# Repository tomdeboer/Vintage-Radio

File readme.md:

*Vintage Radio*
----
This project started out a birthday gift for a friend, but has changed shape many times over the years. The idea was to take a '60s vintage radio and upgrade it as well as I can with stereo, bluetooth, IR remote control, motorised volume knobs and quality >50 W speakers.

Now that the project is really taking shape, I thought: why not make the code and documents open source!

**Note: this is a work in progress at the moment.**

### What can it do?
As mentioned, the radio packs some serious punch when it comes to audio. It can play your tunes loudly and clearly. It also has a bluetooth receiver so you can stream your audio wirelessly. In addition to bluetooth, it has the standard red and white tulip audio jacks and a 3,5 mm audio/headphone jack. The headphone jack is actually an input and has some special functionality: it can mimic headphone controls. This means when you connect your phone to the radio via the headphone jack, your phone will think there's a headphone attached. Together with an infrared receiver, this allows your to control the volume or playback of your phone, as if you were touching the playback controls of your headphone. As a finishing touch, the vintage knobs turn a motorised potentiometer. So when you control the volume externally, i.e. using the remote, the knob will catch up with you and will turn to the appropriate position as if you were turning it yourself!

**Summing up:**

* \>50W audio amplifier
* Bluetooth audio
* Tulip audio connectors
* 3,5mm jack with headphone controls
* Infrared remote
* Self-turning volume knob!

### How do I use it?
The goal of this repository is to provide some sort of manual or inspiration for building your own upgraded vintage radio. It'll contain the Eagle board files of the PCB I designed for the project and there'll be links to all the datasheets you need. The board itself houses a Arduino Pro Mini 5V (for easy development) and contains digital pots for controlling the volume and controlling the headphone functionality. The bluetooth board is a separate RN52 break out board. I used the one from Spark Fun.

### Docs
[Arduino Pro mini](http://www.arduino.cc/en/Main/ArduinoBoardProMini)

[MCP41010 (digital pots)](http://ww1.microchip.com/downloads/en/DeviceDoc/11195c.pdf)

### BOM
- 1x Arduino Pro Mini $10
- 3x MCP41010 $1.50
- 6x 4.7k 5% resistor $1.50
- 10x Screw Terminals (2 conn) 3,5mm grid $5
- 4x Screw Terminals (3 conn) 3,5mm grid $2
- 1x 3.3V converter $2

*Total cost ~$25*

- '60s radio $20
- 35W Amplifier $60
- RN52 Bluetooth break out $40
- 50W JBL car Speakers $75

*Total: ~$195*

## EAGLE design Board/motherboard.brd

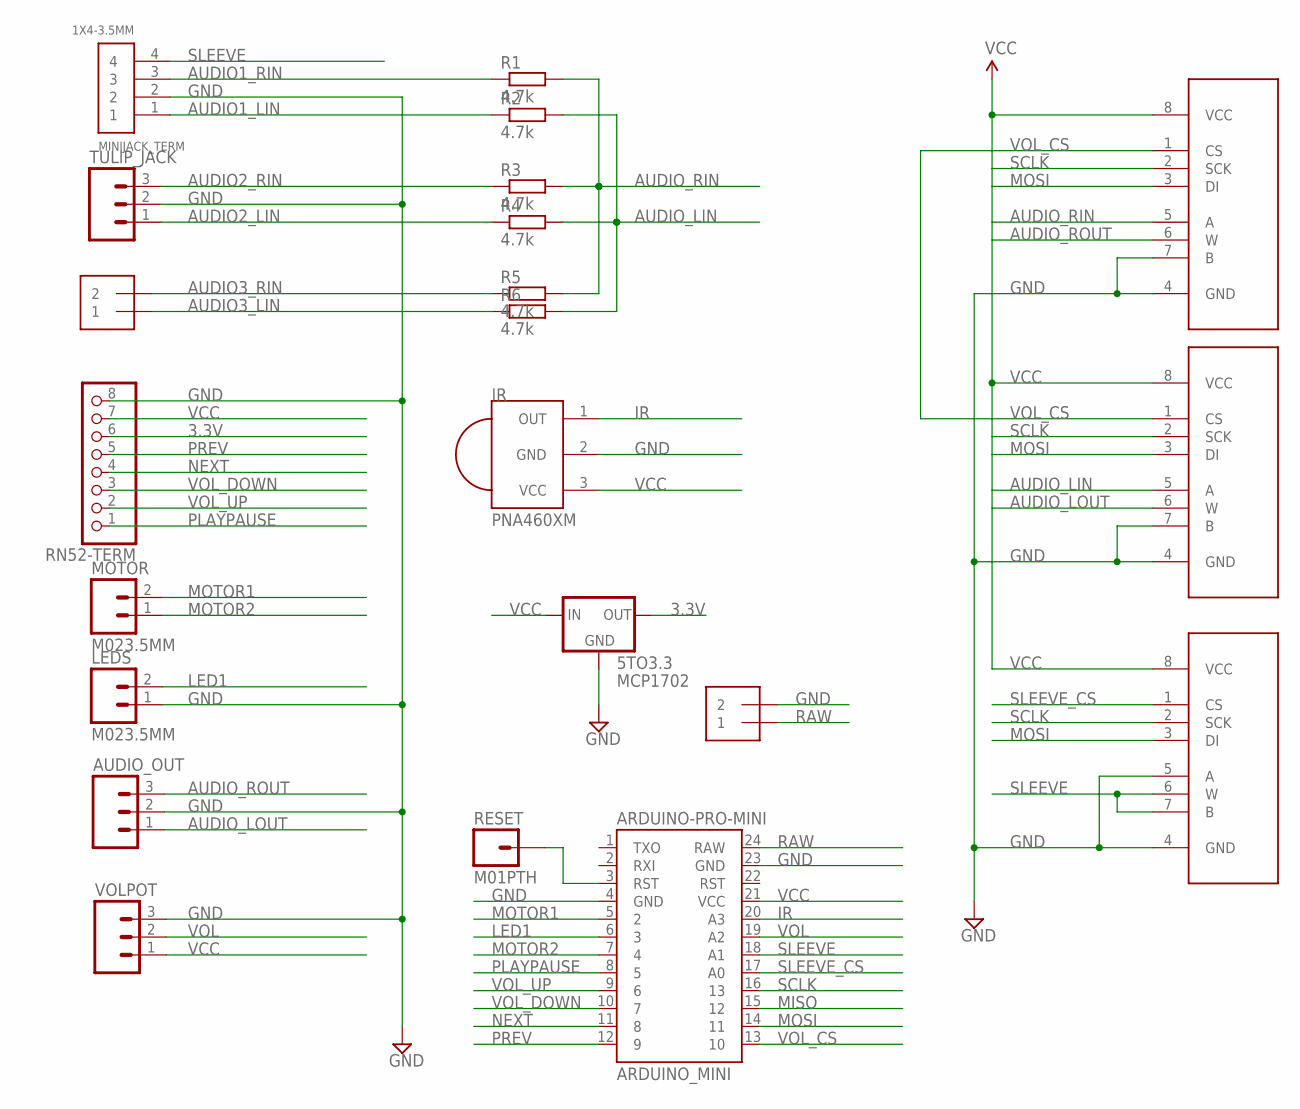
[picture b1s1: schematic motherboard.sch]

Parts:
5TO3.3: MCP1702; TO92-INLINE
ARDUINO-PRO-MINI: ARDUINO_MINI
AUDIO_OUT: M03SCREW; SCREWTERMINAL-3.5MM-3
BL_AUDIO_TERM: 1X2-3.5MM
DPOT_LFT: MCP41XXXDIL; DIL-08
DPOT_RGHT: MCP41XXXDIL; DIL-08
DPOT_SLEEVE: MCP41XXXDIL; DIL-08
IR: PNA460XM
LEDS: M023.5MM; SCREWTERMINAL-3.5MM-2
MINIJACK_TERM: 1X4-3.5MM; 1X04-3.5MM
MOTOR: M023.5MM; SCREWTERMINAL-3.5MM-2
POWER: 1X2-3.5MM
R1, R2, R3, R4, R5, R6: 4.7k; 0207/10
RESET: M01PTH; 1X01
RN52-TERM: PINHD-1X8-3.5MM; 1X08-3.5MM
TULIP_JACK: M03SCREW; SCREWTERMINAL-3.5MM-3
VOLPOT: M03SCREW; SCREWTERMINAL-3.5MM-3

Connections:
3.3V: 5TO3.3.3 (OUT), RN52-TERM.6
AUDIO1_LIN: MINIJACK_TERM.1, R2.1
AUDIO1_RIN: MINIJACK_TERM.3, R1.1
AUDIO2_LIN: R4.1, TULIP_JACK.1
AUDIO2_RIN: R3.1, TULIP_JACK.3
AUDIO3_LIN: BL_AUDIO_TERM.1, R6.1
AUDIO3_RIN: BL_AUDIO_TERM.2, R5.1
AUDIO_LIN: DPOT_LFT.5 (A), R2.2, R4.2, R6.2
AUDIO_LOUT: AUDIO_OUT.1, DPOT_LFT.6 (W)
AUDIO_RIN: DPOT_RGHT.5 (A), R1.2, R3.2, R5.2
AUDIO_ROUT: AUDIO_OUT.3, DPOT_RGHT.6 (W)
GND: 5TO3.3.1 (GND), ARDUINO-PRO-MINI.4 (GND), ARDUINO-PRO-MINI.23 (GND), AUDIO_OUT.2, DPOT_LFT.4 (GND), DPOT_LFT.7 (B), DPOT_RGHT.4 (GND), DPOT_RGHT.7 (B), DPOT_SLEEVE.4 (GND), DPOT_SLEEVE.5 (A), IR.2 (GND), LEDS.1, MINIJACK_TERM.2, POWER.2, RN52-TERM.8, TULIP_JACK.2, VOLPOT.3
IR: ARDUINO-PRO-MINI.20 (A3), IR.1 (OUT)
LED1: ARDUINO-PRO-MINI.6 (3), LEDS.2
MISO: ARDUINO-PRO-MINI.15 (12)
MOSI: ARDUINO-PRO-MINI.14 (11), DPOT_LFT.3 (DI), DPOT_RGHT.3 (DI), DPOT_SLEEVE.3 (DI)
MOTOR1: ARDUINO-PRO-MINI.5 (2), MOTOR.2
MOTOR2: ARDUINO-PRO-MINI.7 (4), MOTOR.1
unnamed: ARDUINO-PRO-MINI.3 (RST), RESET.1
NEXT: ARDUINO-PRO-MINI.11 (8), RN52-TERM.4
PLAYPAUSE: ARDUINO-PRO-MINI.8 (5), RN52-TERM.1
PREV: ARDUINO-PRO-MINI.12 (9), RN52-TERM.5
RAW: ARDUINO-PRO-MINI.24 (RAW), POWER.1
SCLK: ARDUINO-PRO-MINI.16 (13), DPOT_LFT.2 (SCK), DPOT_RGHT.2 (SCK), DPOT_SLEEVE.2 (SCK)
SLEEVE: ARDUINO-PRO-MINI.18 (A1), DPOT_SLEEVE.6 (W), DPOT_SLEEVE.7 (B), MINIJACK_TERM.4
SLEEVE_CS: ARDUINO-PRO-MINI.17 (A0), DPOT_SLEEVE.1 (CS)
VCC: 5TO3.3.2 (IN), ARDUINO-PRO-MINI.21 (VCC), DPOT_LFT.8 (VCC), DPOT_RGHT.8 (VCC), DPOT_SLEEVE.8 (VCC), IR.3 (VCC), RN52-TERM.7, VOLPOT.1
VOL: ARDUINO-PRO-MINI.19 (A2), VOLPOT.2
VOL_CS: ARDUINO-PRO-MINI.13 (10), DPOT_LFT.1 (CS), DPOT_RGHT.1 (CS)
VOL_DOWN: ARDUINO-PRO-MINI.10 (7), RN52-TERM.3
VOL_UP: ARDUINO-PRO-MINI.9 (6), RN52-TERM.2

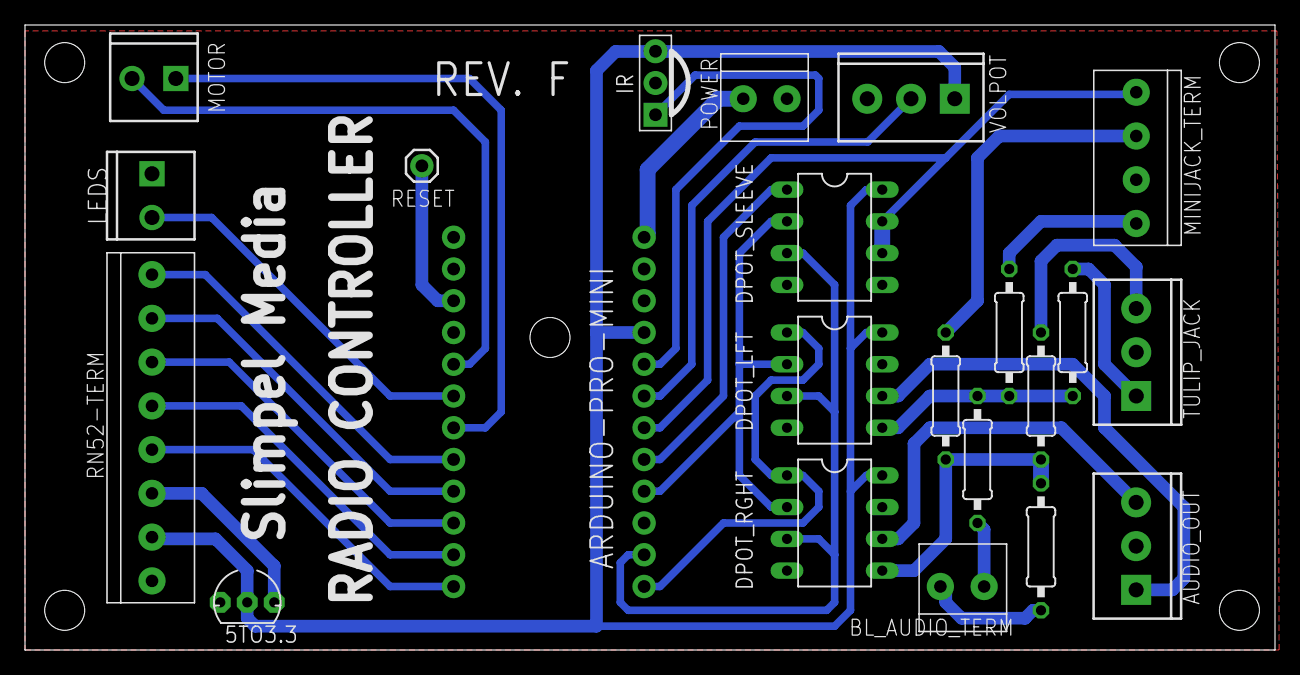
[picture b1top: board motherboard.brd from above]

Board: 2 copper layers, 100.0 x 50.0 mm, 22 parts (0 on the bottom side), 30 nets.

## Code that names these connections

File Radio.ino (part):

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
// Sleeve digital pot
#define PIN_SLEEVE_SL A0
#define PIN_SLEEVE    A1 // This pin is set as input to shorten the mini-jack sleeve pin (used for play/pause toggling)
#define SLEEVE_ANALOG_TRESHOLD 300

typedef enum { CMD_OPEN, CMD_PLAY_PAUSE, CMD_PREV, CMD_NEXT } sleev_command_t;
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#define CMD_NEXT_RESISTANCE 600 // 600 Ohms

// Motor
#define PIN_MOTOR1 2
#define PIN_MOTOR2 4

typedef enum { MOTOR_CLOCKWISE = 1, MOTOR_ANTI_CLOCKWISE = 2, MOTOR_OFF = 0 } motor_setting_e;

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
void task_detect_sleeve(Task* self){

	if ( phone_connected_counter < 5 && analogRead(PIN_SLEEVE) > SLEEVE_ANALOG_TRESHOLD ){
		phone_connected_counter += 1;
	}else if (phone_connected_counter > 0 && analogRead(PIN_SLEEVE) <= SLEEVE_ANALOG_TRESHOLD ) {
		phone_connected_counter -= 1;
	}
	// Serial.print("Phone sleeve value: "); Serial.println(analogRead(SLEEVE_SHORTING_PIN) );
	// Serial.print("Phone connected counter: "); Serial.println(phone_connected_counter);


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	Serial.print("Volume volume:"); Serial.println(volume.value);
	Serial.print("Volume knob  :"); Serial.println((analogRead(PIN_AUDIO_VOL)));

	Serial.print("Sleeve       :"); Serial.println(analogRead(PIN_SLEEVE));
}

void setup() {
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	pinMode (PIN_SLEEVE_SL, OUTPUT);

	// SLEEVE ANALOG
	pinMode (PIN_SLEEVE, INPUT);
	digitalWrite(PIN_SLEEVE, LOW);


	// Start SPI and initialize
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
	// MOTOR
	Serial.print("Motor init...");
	pinMode(PIN_MOTOR1, OUTPUT);
	pinMode(PIN_MOTOR2, OUTPUT);
	Serial.print('.');
	motor_set(MOTOR_ANTI_CLOCKWISE);
	delay(1000);
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			Serial.print("OPEN "); Serial.println("-------");
			SPI.transfer(0x21); // Shutdown. Shorts B (not connected) & W (GND) together and cuts A (Sleeve) loose.
			SPI.transfer(0x0); // Dummy resistance
			pinMode(PIN_SLEEVE, INPUT);
			break;
		case CMD_PLAY_PAUSE:
			Serial.print("Pause "); Serial.println("0  ohm");
			SPI.transfer(0x11); // Write data:
			SPI.transfer(255-0);    // Short it (this makes it play/pause)
			pinMode(PIN_SLEEVE, OUTPUT);
			break;
		case CMD_PREV:
			Serial.print("PREV "); Serial.println("235 ohm");
			SPI.transfer(0x11); // Write data:
			// SPI.transfer(255*(CMD_PREV_RESISTANCE/10000));
			SPI.transfer(255-(6-2));
			pinMode(PIN_SLEEVE, INPUT);
			break;
		case CMD_NEXT:
			Serial.print("CMD_NEXT "); Serial.println("588 ohm");
			SPI.transfer(0x11); // Write data:
			SPI.transfer(255-(15-2));
			pinMode(PIN_SLEEVE, INPUT);
			break;
	}
	
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}

void motor_set(motor_setting_e __setting){
	digitalWrite(PIN_MOTOR1, __setting == MOTOR_CLOCKWISE);
	digitalWrite(PIN_MOTOR2, __setting == MOTOR_ANTI_CLOCKWISE);
	// Serial.print("Direction: "); Serial.println(__setting);
}

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
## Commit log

2014-11-16 First commit
    Lots to be done! Not working entirely.
2014-11-16 Fixed motor controlling
2014-11-16 Added readme
2014-11-17 Added docs and board

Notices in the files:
parts and their libraries:
SparkFun-Connectors: Licensing: Creative Commons ShareAlike 4.0 International - https://creativecommons.org/licenses/by-sa/4.0
